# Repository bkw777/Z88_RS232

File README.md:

# Cambridge Z88 serial port adapters

## PC style

PCB: https://oshpark.com/shared_projects/w1GYezbu  
BOM: https://www.digikey.com/short/zfdrnv

Z88_RS232_PC converts the Z88 serial port to a PC style com port.  
DE9M with standard RS-232 DTE pinout.

This adapter is most convenient for using peripherals designed for use with a standard PC or USB-Serial adapter, or a 9-pin null-modem cable to a PC.

## "Model T" style

PCB: https://oshpark.com/shared_projects/cCj4Skb4  
BOM: https://www.digikey.com/short/zfdrnz

Z88_RS232_Model_T converts the Z88 serial port to a "Model T" style serial port.  
DB25F with standard RS-232 DTE pinout.

This is not like most hosts or devices today, in that normally a DTE or host port is a male plug, but it's otherwise still conforming to the rs232 standard in that the correct rs-232 signals are on the correct pin numbers. It's only the female connector that's unusual.

"Model T" computers are: TRS-80/TANDY Models 100, 102, 200, 600, NEC Models PC-8201, PC-8201A, PC-8300, Olivetti M10, and Kyotronic KC-85. All of these machines have a DB25F connectore with a RS-232 DTE pinout.

This adapter is most convenient for using peripherals designed for use with "Model T" computers, for instance the Tandy Portable Disk Drive.

You could connect to a PC with this adapter too, by using the same slightly uncommon kind of cable that a "model T" would need.  
http://tandy.wiki/Model_T_Serial_Cable

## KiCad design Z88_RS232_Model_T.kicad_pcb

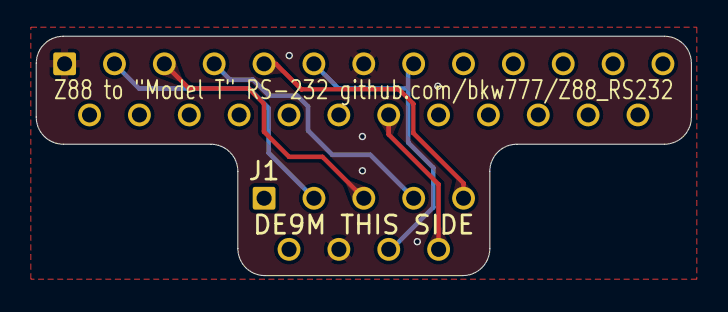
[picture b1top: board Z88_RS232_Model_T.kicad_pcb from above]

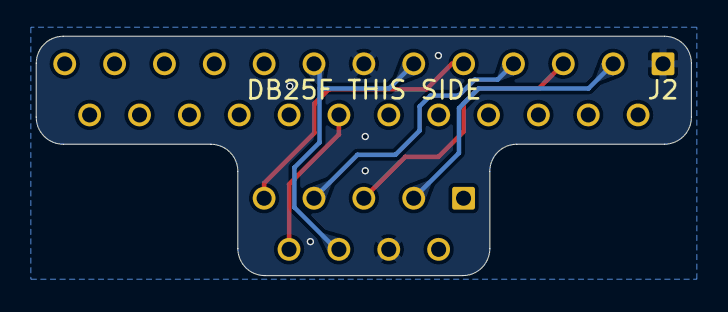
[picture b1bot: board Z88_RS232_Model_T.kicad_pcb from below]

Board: 2 copper layers, 36.4 x 13.3 mm, 3 parts (2 on the bottom side), 8 nets.

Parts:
J1: DE9_Male; DSUB-9_Male_Vertical_P2.77x2.84mm
J2: DB25 Female; DSUB-25_Female_Vertical_P2.77x2.84mm
NT1: Net-Tie_2; NetTie-2_SMD_10

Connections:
/CTS: J1.5, J2.5
/DCD: J1.8, J2.8, NT1.1
/DSR: J2.6, NT1.2
/DTR: J1.9, J2.20
/RTS: J1.4, J2.4
/RX: J1.3, J2.3
/TX: J1.2, J2.2
GND: J1.7, J2.1, J2.7

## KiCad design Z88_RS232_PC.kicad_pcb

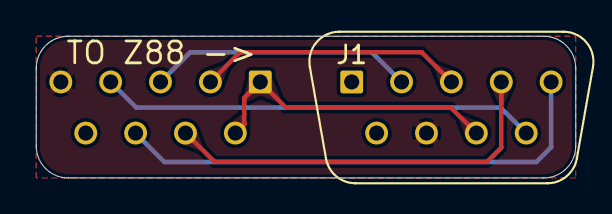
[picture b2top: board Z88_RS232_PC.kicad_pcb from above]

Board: 2 copper layers, 30.0 x 7.9 mm, 3 parts (1 on the bottom side), 8 nets.

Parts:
J1, J2: DE9_Male; DSUB-9_Male_Vertical_P2.77x2.84mm
NT1: Net-Tie_2; NetTie-2_SMD_10

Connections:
/CTS: J1.5, J2.8
/DCD: J1.8, J2.1, NT1.1
/DSR: J2.6, NT1.2
/DTR: J1.9, J2.4
/RTS: J1.4, J2.7
/RX: J1.3, J2.2
/TX: J1.2, J2.3
GND: J1.7, J2.5

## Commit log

2020-09-09 initial
2020-09-09 pcbs & boms
2024-05-06 kicad8, increase model-t pcb size
